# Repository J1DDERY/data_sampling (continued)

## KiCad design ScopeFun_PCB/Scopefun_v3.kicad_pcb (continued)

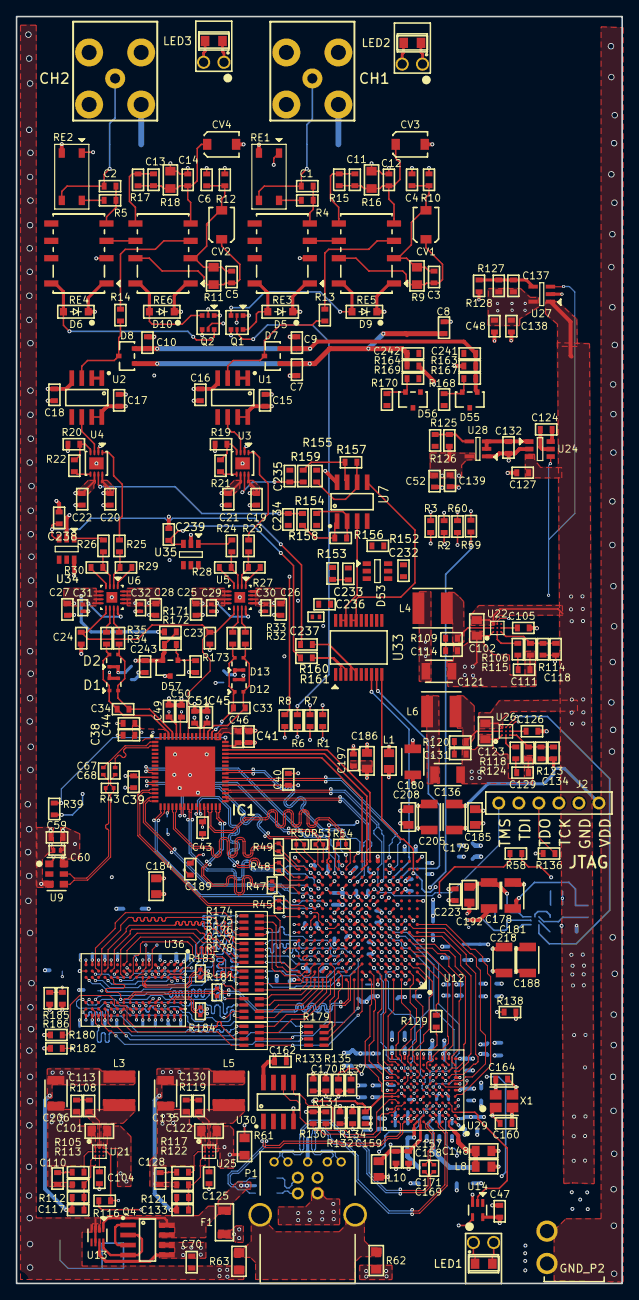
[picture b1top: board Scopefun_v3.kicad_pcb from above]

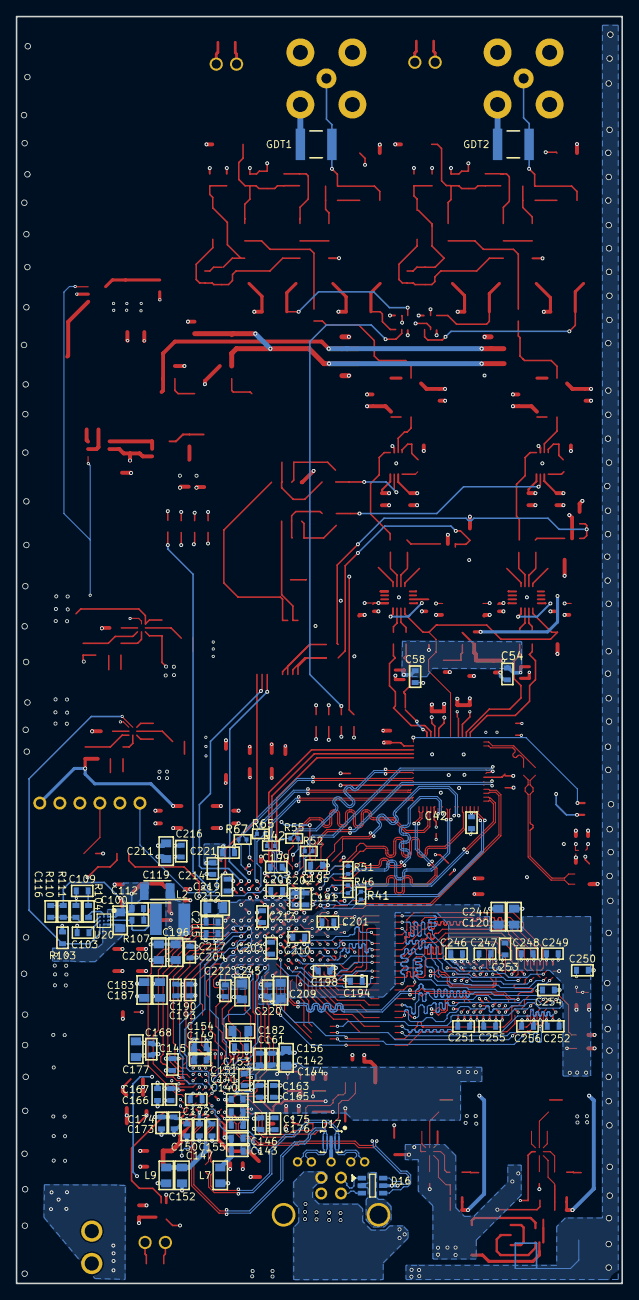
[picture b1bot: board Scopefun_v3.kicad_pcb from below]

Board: 6 copper layers, 76.8 x 160.6 mm, 405 parts (102 on the bottom side), 333 nets.

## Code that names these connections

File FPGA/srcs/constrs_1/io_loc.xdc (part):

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# PadFunction: IO_L12N_T1_MRCC_14
# clk_adc_n 固定在 N-side pad（P14），避免 IBUFDS DRC 错误。
set_property IOSTANDARD LVDS_25 [get_ports clk_adc_n]
set_property PACKAGE_PIN N14 [get_ports clk_adc_p]
set_property PACKAGE_PIN P14 [get_ports clk_adc_n]

set_property IOSTANDARD LVCMOS33 [get_ports dasync]
set_property IOSTANDARD LVCMOS33 [get_ports dasdin]
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set_property IOSTANDARD LVCMOS18 [get_ports slwr]
set_property IOSTANDARD LVCMOS18 [get_ports slcs]
set_property IOSTANDARD LVCMOS18 [get_ports pktend]
set_property PACKAGE_PIN T8 [get_ports adc_sdin]
set_property PACKAGE_PIN R8 [get_ports adc_sclk]
set_property PACKAGE_PIN T7 [get_ports adcA_cs]


set_property PACKAGE_PIN C1 [get_ports clk_fx3]
set_property PACKAGE_PIN N12 [get_ports ch2_dc]
set_property PACKAGE_PIN R12 [get_ports ch1_dc]
set_property PACKAGE_PIN M12 [get_ports ch1_gnd]
set_property PACKAGE_PIN N13 [get_ports ch2_gnd]

set_property PACKAGE_PIN N4 [get_ports dasync]
set_property PACKAGE_PIN N3 [get_ports dasdin]
set_property PACKAGE_PIN M4 [get_ports dasclk]

set_property PACKAGE_PIN M15 [get_ports ch2_k]
set_property PACKAGE_PIN P13 [get_ports ch1_k]
set_property PACKAGE_PIN L5 [get_ports {LED[2]}]
set_property PACKAGE_PIN M5 [get_ports {LED[3]}]
set_property PACKAGE_PIN L4 [get_ports {LED[1]}]
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set_property PACKAGE_PIN H3 [get_ports {fdata[31]}]
set_property PACKAGE_PIN D1 [get_ports {faddr[1]}]
set_property PACKAGE_PIN F3 [get_ports {faddr[0]}]
set_property PACKAGE_PIN D3 [get_ports flaga]
set_property PULLDOWN true [get_ports flaga]
set_property PACKAGE_PIN E5 [get_ports flagb]
set_property PULLDOWN true [get_ports flagb]
set_property PACKAGE_PIN E3 [get_ports flagd]
set_property PULLUP true [get_ports flagd]
set_property PACKAGE_PIN C3 [get_ports slrd_sloe]
set_property PACKAGE_PIN C2 [get_ports slwr]
set_property PACKAGE_PIN B1 [get_ports slcs]
set_property PACKAGE_PIN C4 [get_ports pktend]

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
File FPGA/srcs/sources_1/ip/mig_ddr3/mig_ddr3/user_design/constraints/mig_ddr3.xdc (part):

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# PadFunction: IO_L2P_T0_AD8P_15 
set_property SLEW FAST [get_ports {ddr3_cke[0]}]
set_property IOSTANDARD SSTL15 [get_ports {ddr3_cke[0]}]
set_property PACKAGE_PIN A8 [get_ports {ddr3_cke[0]}]

# PadFunction: IO_L1N_T0_AD0N_15 
set_property SLEW FAST [get_ports {ddr3_odt[0]}]
set_property IOSTANDARD SSTL15 [get_ports {ddr3_odt[0]}]
set_property PACKAGE_PIN C9 [get_ports {ddr3_odt[0]}]

# PadFunction: IO_L21P_T3_DQS_15 
set_property SLEW FAST [get_ports {ddr3_dqs_p[0]}]
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# PadFunction: IO_L3P_T0_DQS_AD1P_15 
set_property SLEW FAST [get_ports {ddr3_ck_p[0]}]
set_property IOSTANDARD DIFF_SSTL15 [get_ports {ddr3_ck_p[0]}]
set_property PACKAGE_PIN B9 [get_ports {ddr3_ck_p[0]}]

# PadFunction: IO_L3N_T0_DQS_AD1N_15 
set_property SLEW FAST [get_ports {ddr3_ck_n[0]}]
set_property IOSTANDARD DIFF_SSTL15 [get_ports {ddr3_ck_n[0]}]
set_property PACKAGE_PIN A10 [get_ports {ddr3_ck_n[0]}]


set_property INTERNAL_VREF  0.750 [get_iobanks 15]
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
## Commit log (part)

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2026-03-23 gitignore
2026-03-23 initial
2026-03-26 0326
2026-03-30 260330
2026-04-07 260407
2026-04-09 260409
2026-04-09 260409_1
2026-04-11 260410
2026-04-12 260412
2026-04-12 260412_1
2026-04-12 260412_2
2026-04-17 260417_diff_comp
2026-04-17 260417_CHANGED
2026-04-20 260420
2026-04-21 260421
2026-04-21 260421_1
2026-04-23 implemented
2026-05-07 manufactured
2026-05-15 260515
2026-05-15 no_ETS
2026-05-15 260515_1
2026-05-16 260516
2026-05-17 260517
2026-05-18 10bittrig
2026-05-18 no_CR
2026-05-20 260520
2026-05-22 260522
2026-05-27 0527_dacchange
2026-05-31 0531
2026-06-02 260601
2026-06-10 260610_runable
2026-06-21 0621
